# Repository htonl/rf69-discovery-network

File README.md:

This is the network library for the ALog by Northern Widget. This was developed
by Luke Cesarz, Jeff Worm, and David Nickel

This repo contains 2 branches:
master                      //Implemented with low power lab lib
feather-version             //Implemented with feather

The feather-version branch is the version of the code that was working on the
M0. We had a zero acting as coord with two pros sending it data flawlessly.
I think we then made a change to test something and broke it.

Both libraries work with the arduino pro.

The reason we have both libraries is SPI. SPI setup in the low power lab library
is not working on the M0, but the SPI setup in feather does work with the M0.

The issue in the feather-version can be described like so:
When we get to transmission, the radio reaches a stand still and the code
deadlocks. It is marked in the file where we suspect this is happening. It is in
the RH_RF69.cpp file.

It happens when we call sendToWait()

The files we added:
Network.h           //Self discovery algorithm and communication protocol
Network.cpp         // ''
Queue.cpp           //The queue for storing the data to send
Queue.h             //''
Packet.h            //The packet stucture we designed for communication

DESCRIPTION OF HOW THE NETWORK: I WROTE THIS A WHILE AGO, BUT IT IS STILL A GOOD
DESCRIPTION -LUKE

This code is meant to interface with the Alog library by Northern Widget. When
completed, this implementation will include radio telemetry using the RFM69 chip
for RF communication. This library is currently a work in progress and should
not be expected to work on its own. Expect a working copy in early May.
The new libraries in this repo are the Network.cpp, Network.h, Queue.cpp,
Queue.h, and Packet.h files. In total about 650 lines of code were added.

How to use the Network:

In order to use the network in the Logger Library, the user need only call 2
functions: sendOverNetwork(float data) with a floating point of the data that
they want to send to the coord, and then runNetwork(). runNetwork() is the
heart of the network library. It takes care of keeping up each nodes connection
to the coordinator, and handling any packets it receives or needs to send. A 
more detailed description of the algorithm can be found below, but these two
functions are all the end user NEEDS to get the network rolling.

A more detailed description:

The network algorithm works like so in pseudocode:

runNetwork()
{
	//condition 1 we are the coord listen for data
	if(IamCoord)
	{
		listen for incoming data and upload it to server
	}
	//condition 2 we have a connection to the coord, send data
	else if(IhaveConnectionToCoord)
	{
		send all of my data towards coord
		listen for data to forward to coord
	}
	//condition 3 we do not have connection to the coord
	else
	{
		try to connect to coordinator
	}
}
A few notable points in this algorithm. Originally, we were trying to forward
the data from the furthest leaf nodes to the router nodes first, then forward it
to the coordinator, but there is a nightmare of timing issues and other
complexities. Then we decided to do the opposite:send the data from the closest
nodes to the coordinator first. Therefore in condition 2, all the nodes that
aren't coord will be sending their data over and over again until it finally
reaches the coordinator. Then they will start listening for other nodes that
are using them as a next hop to get to the coord, and forward that data. This
eliminates a lot of the timing issues, and the need for each node to know the
other nodes depending on it.

Data logger library for the Arduino-based ALog (http://northernwidget.com/?page_id=8)

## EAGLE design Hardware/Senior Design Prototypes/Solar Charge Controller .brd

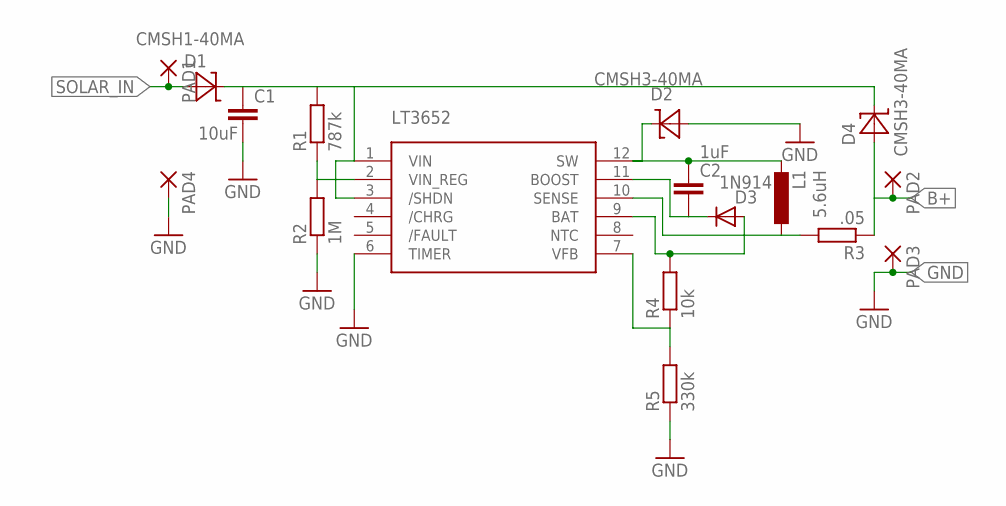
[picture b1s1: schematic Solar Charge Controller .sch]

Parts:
C1: 10uF; C0805
C2: 1uF; C0603
D1: CMSH1-40MA; DO-214AC
D2, D4: CMSH3-40MA; DO-214AC
D3: 1N914; SOD523
L1: 5.6uH; 1008(2510METRIC)
PAD1, PAD2, PAD3, PAD4: SMD5; SMD2,54-5,08
R1: 787k; R0603
R2: 1M; R0603
R3: .05; R0805
R4: 10k; R0603
R5: 330k; R0603
U$1: LT3652; MSOP12

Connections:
B+: D4.A, PAD2.1, R3.1
GND: C1.2, D2.A, PAD3.1, PAD4.1, R2.1, R5.1, U$1.6 (TIMER)
unnamed: C1.1, D1.C, D4.C, R1.2, U$1.1 (VIN), U$1.3 (/SHDN)
unnamed: R1.1, R2.2, U$1.2 (VIN_REG)
unnamed: C2.1, D2.C, L1.P$3 (2), U$1.12 (SW)
unnamed: L1.P$2 (1), R3.2, U$1.10 (SENSE)
unnamed: D3.A, R4.2, U$1.9 (BAT)
unnamed: C2.2, D3.C, U$1.11 (BOOST)
unnamed: R4.1, R5.2, U$1.7 (VFB)
SOLAR_IN: D1.A, PAD1.1

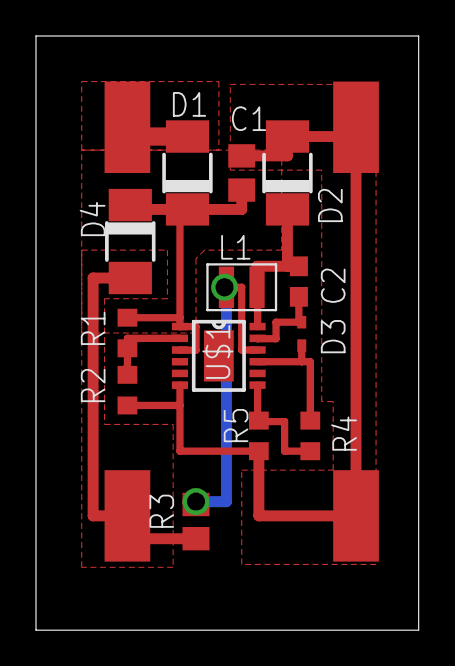
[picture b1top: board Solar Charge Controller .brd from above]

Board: 2 copper layers, 21.3 x 33.0 mm, 17 parts (0 on the bottom side), 10 nets.

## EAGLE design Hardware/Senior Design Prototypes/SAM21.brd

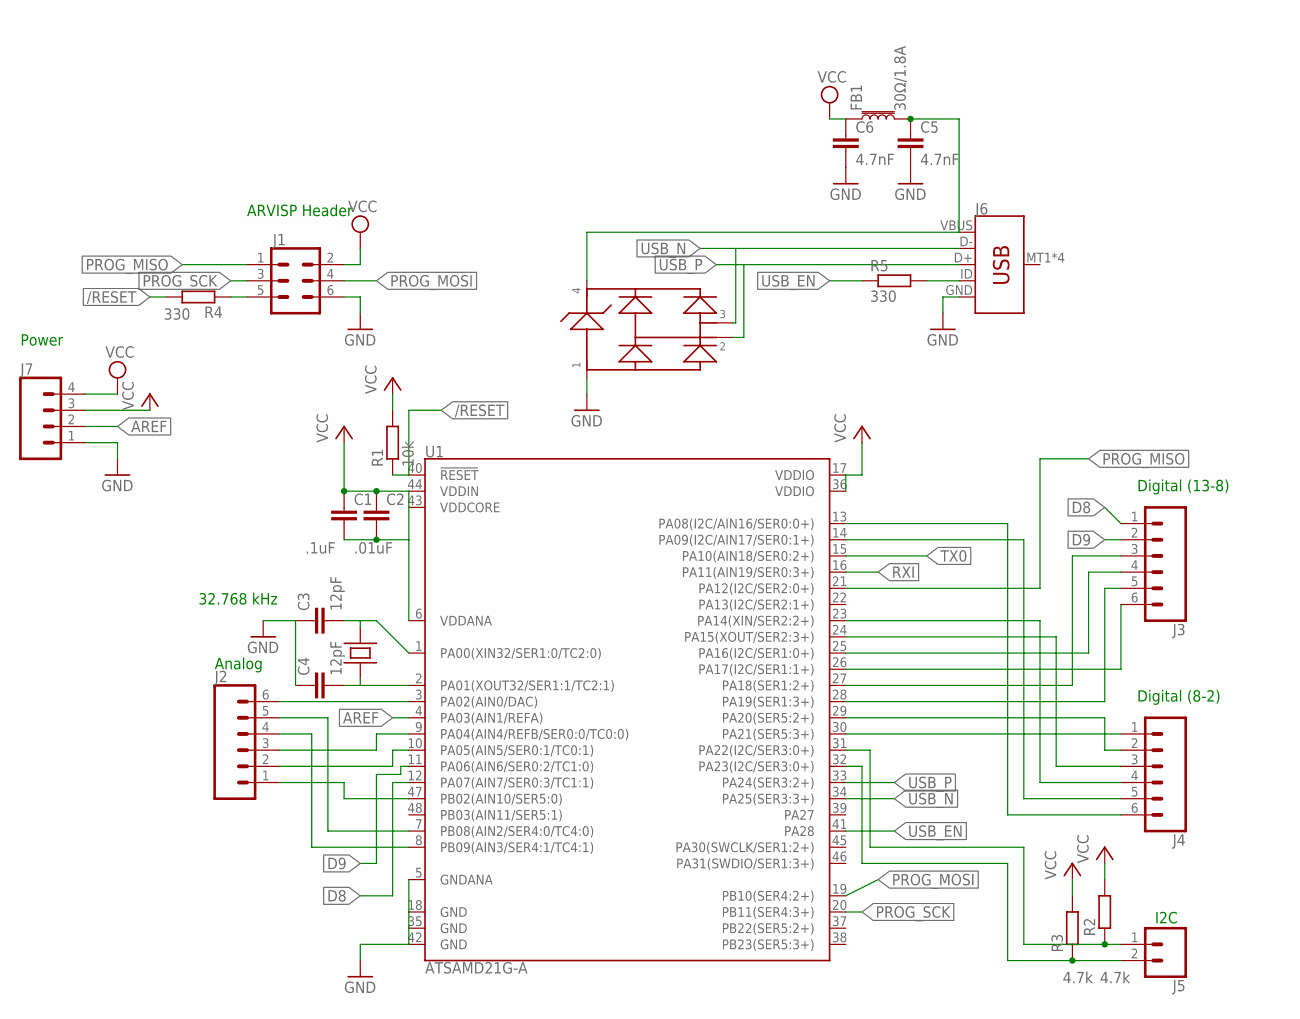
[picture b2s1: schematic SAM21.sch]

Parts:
C1: .1uF; C0603
C2: .01uF; C0603
C3, C4: 12pF; C0603
C5, C6: 4.7nF; C0603
FB1: 30Ω/1.8A; 0603
J1: CONN_03X2FEMALE_SMD; 2X3_SMD
J2, J3, J4: CONN_06LONGPADS; 1X06_LONGPADS
J5: CONN_02PTH3; 1X02_LONGPADS
J6: USB_MICRO-B_SMT; USB-MICROB
J7: CONN_04LONGPADS; 1X04_LONGPADS
R1: 10k; R0603
R2, R3: 4.7k; R0603
R4, R5: 330; R0603
U1: ATSAMD21G-A; TQFP-48
U$1: CM200; 4-SOJ
U$2: PRTR5V0U2X; SOT143B

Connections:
5V: J1.2
/RESET: R1.1, R4.2, U1.40 (!RESET!)
AREF: J7.2, U1.4 (PA03(AIN1/REFA))
D8: J3.1, U1.12 (PA07(AIN7/SER0:3/TC1:1))
D9: J2.4, J3.2, U1.8 (PB09(AIN3/SER4:1/TC4:1)), U1.11 (PA06(AIN6/SER0:2/TC1:0))
GND: C3.1, C4.1, C5.2, C6.2, J1.6, J6.GND, J7.1, U1.5 (GNDANA), U1.18 (GND), U1.35 (GND), U1.42 (GND), U$2.P$1 (1)
unnamed: J4.1, U1.30 (PA21(SER5:3+))
unnamed: J2.6, U1.3 (PA02(AIN0/DAC))
unnamed: J2.5, U1.7 (PB08(AIN2/SER4:0/TC4:0))
unnamed: J4.2, U1.29 (PA20(SER5:2+))
unnamed: J2.3, U1.9 (PA04(AIN4/REFB/SER0:0/TC0:0))
unnamed: J2.2, U1.10 (PA05(AIN5/SER0:1/TC0:1))
unnamed: J2.1, U1.47 (PB02(AIN10/SER5:0))
unnamed: J3.6, U1.26 (PA17(I2C/SER1:1+))
unnamed: J3.5, U1.28 (PA19(SER1:3+))
unnamed: J3.4, U1.25 (PA16(I2C/SER1:0+))
unnamed: J3.3, U1.27 (PA18(SER1:2+))
unnamed: J4.3, U1.24 (PA15(XOUT/SER2:3+))
unnamed: J4.4, U1.23 (PA14(XIN/SER2:2+))
unnamed: J4.5, U1.14 (PA09(I2C/AIN17/SER0:1+))
unnamed: J4.6, U1.13 (PA08(I2C/AIN16/SER0:0+))
unnamed: U1.17 (VDDIO), U1.36 (VDDIO)
unnamed: J5.1, R2.1, U1.31 (PA22(I2C/SER3:0+))
unnamed: C4.2, U1.2 (PA01(XOUT32/SER1:1/TC2:1)), U$1.P$1
unnamed: J5.2, R3.1, U1.32 (PA23(I2C/SER3:0+))
unnamed: J1.5, R4.1
unnamed: C3.2, U1.1 (PA00(XIN32/SER1:0/TC2:0)), U$1.P$4
unnamed: C5.1, FB1.2, J6.VBUS, U$2.P$4 (4)
unnamed: J6.ID, R5.2
PROG_MISO: J1.1, U1.21 (PA12(I2C/SER2:0+))
PROG_MOSI: J1.4, U1.19 (PB10(SER4:2+))
PROG_SCK: J1.3, U1.20 (PB11(SER4:3+))
RXI: U1.16 (PA11(AIN19/SER0:3+))
TX0: U1.15 (PA10(AIN18/SER0:2+))
USB_EN: R5.1, U1.41 (PA28)
USB_N: J6.D-, U1.34 (PA25(SER3:3+)), U$2.P$3 (3)
USB_P: J6.D+, U1.33 (PA24(SER3:2+)), U$2.P$2 (2)
VCC: C1.1, C1.2, C2.1, C2.2, C6.1, FB1.1, J7.3, J7.4, R1.2, R2.2, R3.2, U1.6 (VDDANA), U1.43 (VDDCORE), U1.44 (VDDIN)

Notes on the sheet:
ARVISP Header
Analog
Digital (13-8)
Digital (8-2)
I2C
32.768 kHz
Power

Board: 2 copper layers, 22 parts (0 on the bottom side), 35 nets, no tracks yet.

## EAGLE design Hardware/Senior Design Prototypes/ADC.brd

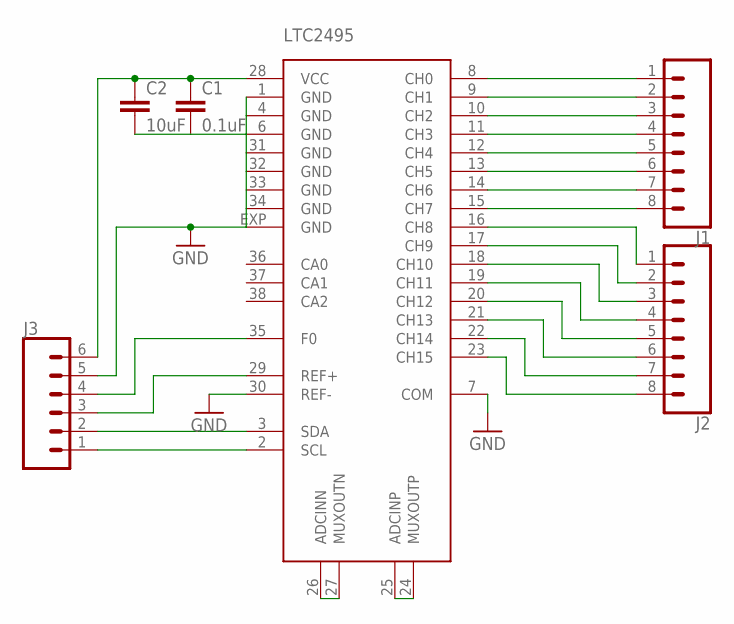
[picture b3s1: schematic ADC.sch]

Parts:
C1: 0.1uF; C0603
C2: 10uF; C0805
J1, J2: CONN_08LONGPADS; 1X08_LONGPADS
J3: CONN_06LONGPADS; 1X06_LONGPADS
U$1: LTC2495; QFN38-5X7

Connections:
GND: C1.2, C2.2, J3.5, U$1.1 (GND), U$1.4 (GND), U$1.6 (GND), U$1.7 (COM), U$1.30 (REF-), U$1.31 (GND), U$1.32 (GND), U$1.33 (GND), U$1.34 (GND), U$1.EXP (GND)
unnamed: J3.1, U$1.2 (SCL)
unnamed: J3.2, U$1.3 (SDA)
unnamed: J3.3, U$1.29 (REF+)
unnamed: J3.4, U$1.35 (F0)
unnamed: C1.1, C2.1, J3.6, U$1.28 (VCC)
unnamed: U$1.26 (ADCINN), U$1.27 (MUXOUTN)
unnamed: U$1.24 (MUXOUTP), U$1.25 (ADCINP)
unnamed: J1.8, U$1.15 (CH7)
unnamed: J1.7, U$1.14 (CH6)
unnamed: J1.6, U$1.13 (CH5)
unnamed: J1.5, U$1.12 (CH4)
unnamed: J1.4, U$1.11 (CH3)
unnamed: J1.3, U$1.10 (CH2)
unnamed: J1.2, U$1.9 (CH1)
unnamed: J1.1, U$1.8 (CH0)
unnamed: J2.1, U$1.16 (CH8)
unnamed: J2.2, U$1.17 (CH9)
unnamed: J2.3, U$1.18 (CH10)
unnamed: J2.4, U$1.19 (CH11)
unnamed: J2.5, U$1.20 (CH12)
unnamed: J2.6, U$1.21 (CH13)
unnamed: J2.7, U$1.22 (CH14)
unnamed: J2.8, U$1.23 (CH15)

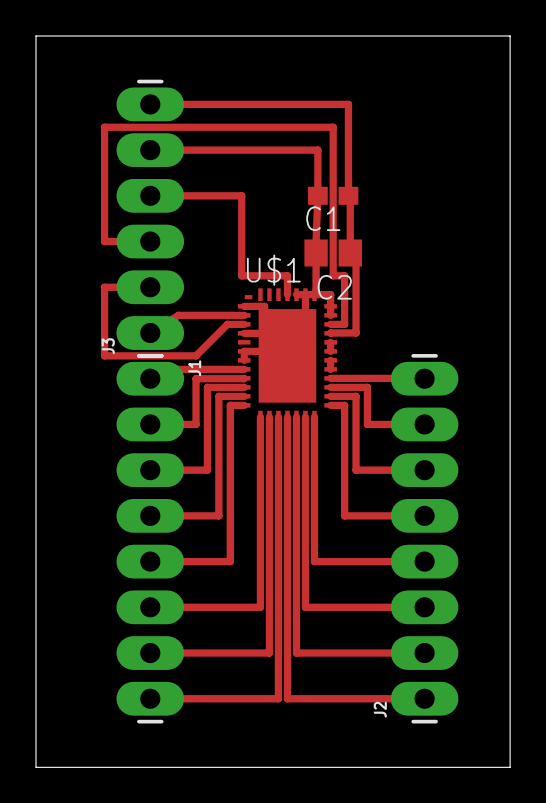
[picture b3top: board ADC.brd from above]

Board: 2 copper layers, 26.3 x 40.6 mm, 6 parts (0 on the bottom side), 24 nets.

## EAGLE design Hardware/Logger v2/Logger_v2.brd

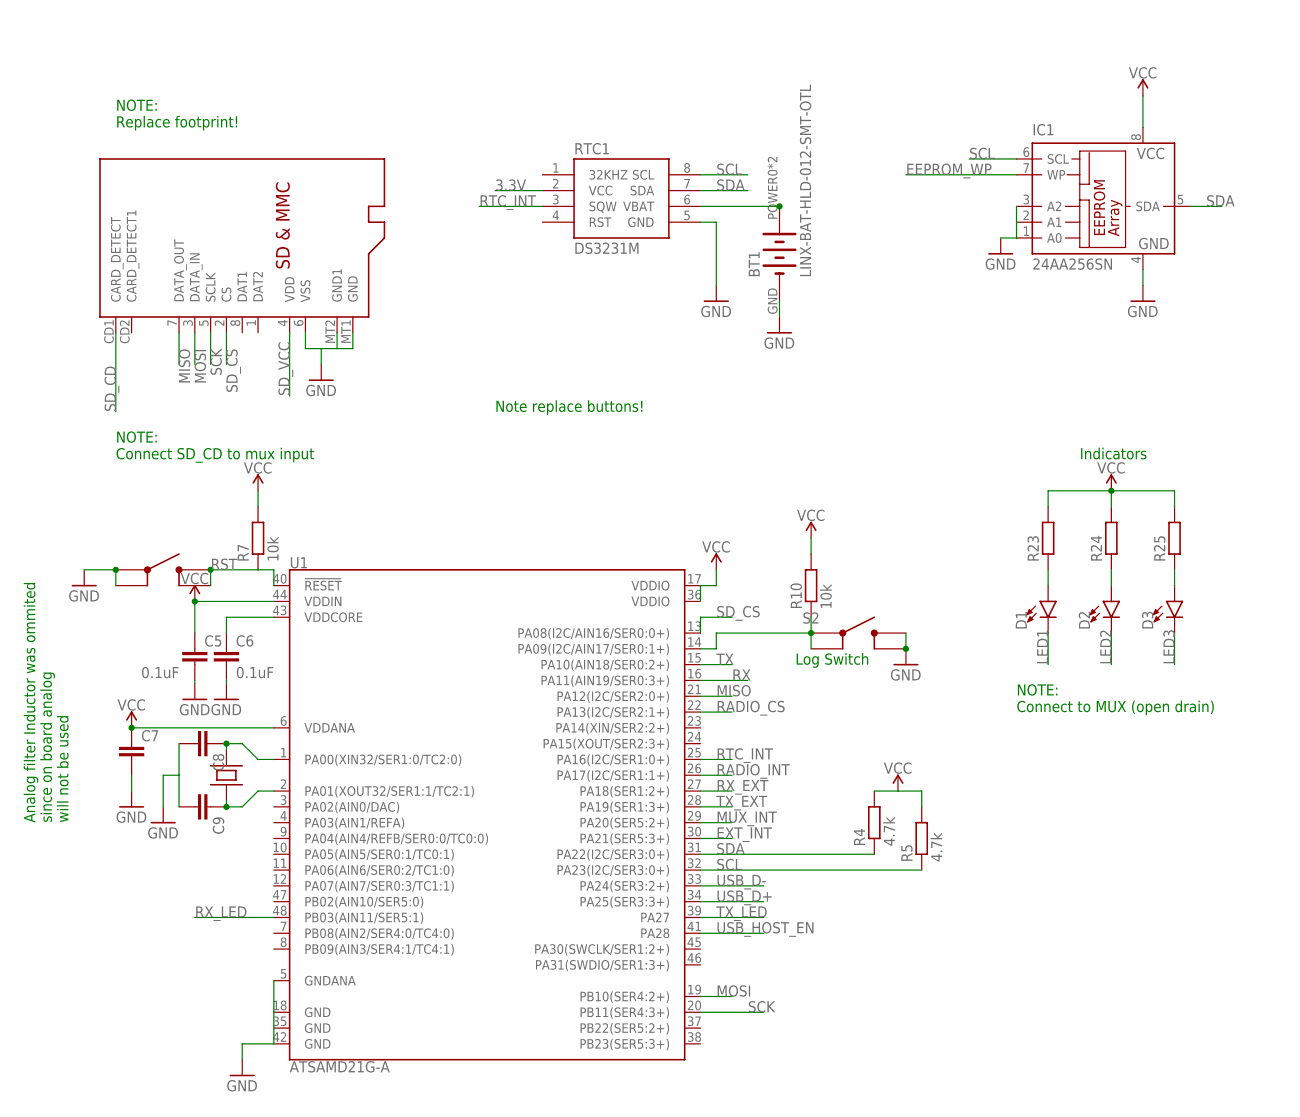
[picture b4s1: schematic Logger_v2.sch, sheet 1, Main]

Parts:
BT1: LINX-BAT-HLD-012-SMT-OTL; LINX_BAT-HLD-012-SMT
C5, C6: 0.1uF; C0603
C7, C8, C9: C-EUC0603; C0603
D1, D2, D3: LED0603; LED-0603
IC1: 24AA256SN; SO-08
R4, R5: 4.7k; R0603
R7, R10: 10k; R0603
R23, R24, R25: R-EU_R0603; R0603
RTC1: DS3231M; SO08
S2: SKRPABE010; SKRPABE010_(SWITCH)
U1: ATSAMD21G-A; TQFP-48
U$1: SKRPABE010; SKRPABE010_(SWITCH)
U$2: MICROSD
U$5: CM200; 4-SOJ

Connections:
3.3V: C5.1, C7.1, IC1.8 (VCC), R4.2, R5.2, R7.2, R10.2, R23.2, R24.2, R25.2, RTC1.2 (VCC), U1.6 (VDDANA), U1.17 (VDDIO), U1.36 (VDDIO), U1.44 (VDDIN); also elsewhere on the board
EEPROM_WP: IC1.7 (WP)
EXT_INT: U1.30 (PA21(SER5:3+)); also elsewhere on the board
GND: BT1.GND (-), C5.2, C6.2, C7.2, C8.2, C9.2, IC1.1 (A0), IC1.2 (A1), IC1.3 (A2), IC1.4 (GND), RTC1.5 (GND), S2.P$3 (3), S2.P$4 (4), U1.5 (GNDANA), U1.18 (GND), U1.42 (GND), U$1.P$1 (1), U$1.P$2 (2), U$2.6 (VSS), U$2.MT1 (GND), U$2.MT2 (GND1); also elsewhere on the board
LED1: D1.C; also elsewhere on the board
LED2: D2.C; also elsewhere on the board
LED3: D3.C; also elsewhere on the board
MISO: U1.21 (PA12(I2C/SER2:0+)), U$2.7 (DATA_OUT); also elsewhere on the board
MOSI: U1.19 (PB10(SER4:2+)), U$2.3 (DATA_IN); also elsewhere on the board
MUX_INT: U1.29 (PA20(SER5:2+)); also elsewhere on the board
unnamed: R10.1, S2.P$1 (1), S2.P$2 (2), U1.14 (PA09(I2C/AIN17/SER0:1+))
unnamed: C6.1, U1.43 (VDDCORE)
unnamed: C8.1, U1.1 (PA00(XIN32/SER1:0/TC2:0)), U$5.P$4
unnamed: C9.1, U1.2 (PA01(XOUT32/SER1:1/TC2:1)), U$5.P$1
unnamed: BT1.POWER0 (+), BT1.POWER1 (+), RTC1.6 (VBAT)
unnamed: D1.A, R23.1
unnamed: D2.A, R24.1
unnamed: D3.A, R25.1
RADIO_CS: U1.22 (PA13(I2C/SER2:1+)); also elsewhere on the board
RADIO_INT: U1.26 (PA17(I2C/SER1:1+)); also elsewhere on the board
RST: R7.1, U1.40 (!RESET!), U$1.P$3 (3), U$1.P$4 (4); also elsewhere on the board
RTC_INT: RTC1.3 (SQW), U1.25 (PA16(I2C/SER1:0+))
RX: U1.16 (PA11(AIN19/SER0:3+))
RX_EXT: U1.27 (PA18(SER1:2+)); also elsewhere on the board
RX_LED: U1.48 (PB03(AIN11/SER5:1))
SCK: U1.20 (PB11(SER4:3+)), U$2.5 (SCLK); also elsewhere on the board
SCL: IC1.6 (SCL), R5.1, RTC1.8 (SCL), U1.32 (PA23(I2C/SER3:0+)); also elsewhere on the board
SDA: IC1.5 (SDA), R4.1, RTC1.7 (SDA), U1.31 (PA22(I2C/SER3:0+)); also elsewhere on the board
SD_CD: U$2.CD1 (CARD_DETECT)
SD_CS: U1.13 (PA08(I2C/AIN16/SER0:0+)), U$2.2 (CS)
SD_VCC: U$2.4 (VDD); also elsewhere on the board
TX: U1.15 (PA10(AIN18/SER0:2+))
TX_EXT: U1.28 (PA19(SER1:3+)); also elsewhere on the board
TX_LED: U1.39 (PA27)
USB_D+: U1.34 (PA25(SER3:3+)); also elsewhere on the board
USB_D-: U1.33 (PA24(SER3:2+)); also elsewhere on the board
USB_HOST_EN: U1.41 (PA28); also elsewhere on the board

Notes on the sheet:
NOTE: Replace footprint!
Log Switch
Analog filter Inductor was ommited since on board analog will not be used
Indicators
NOTE: Connect to MUX (open drain)
NOTE: Connect SD_CD to mux input
Note replace buttons!

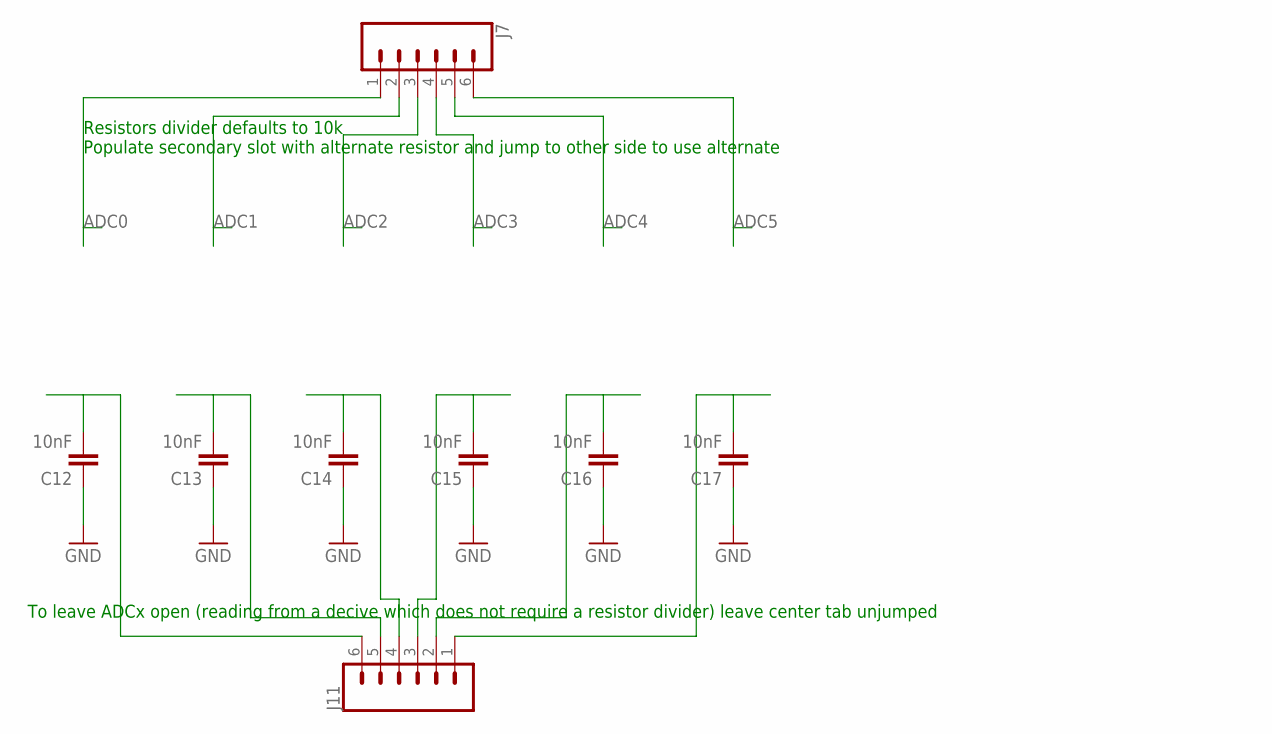
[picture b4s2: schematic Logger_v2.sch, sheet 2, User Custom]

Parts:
C12, C13, C14, C15, C16, C17: 10nF; C0603
J7, J11: CONN_06SMD-STRAIGHT-FEMALE; 1X06_SMD_STRAIGHT

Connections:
ADC0: J7.1; also elsewhere on the board
ADC1: J7.2; also elsewhere on the board
ADC2: J7.3; also elsewhere on the board
ADC3: J7.4; also elsewhere on the board
ADC4: J7.5; also elsewhere on the board
ADC5: J7.6; also elsewhere on the board
GND: C12.1, C13.1, C14.1, C15.1, C16.1, C17.1; also elsewhere on the board
unnamed: C12.2, J11.6
unnamed: C13.2, J11.5
unnamed: C14.2, J11.4
unnamed: C15.2, J11.3
unnamed: C16.2, J11.2
unnamed: C17.2, J11.1

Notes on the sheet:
Resistors divider defaults to 10k Populate secondary slot with alternate resistor and jump to other side to use alternate
To leave ADCx open (reading from a decive which does not require a resistor divider) leave center tab unjumped

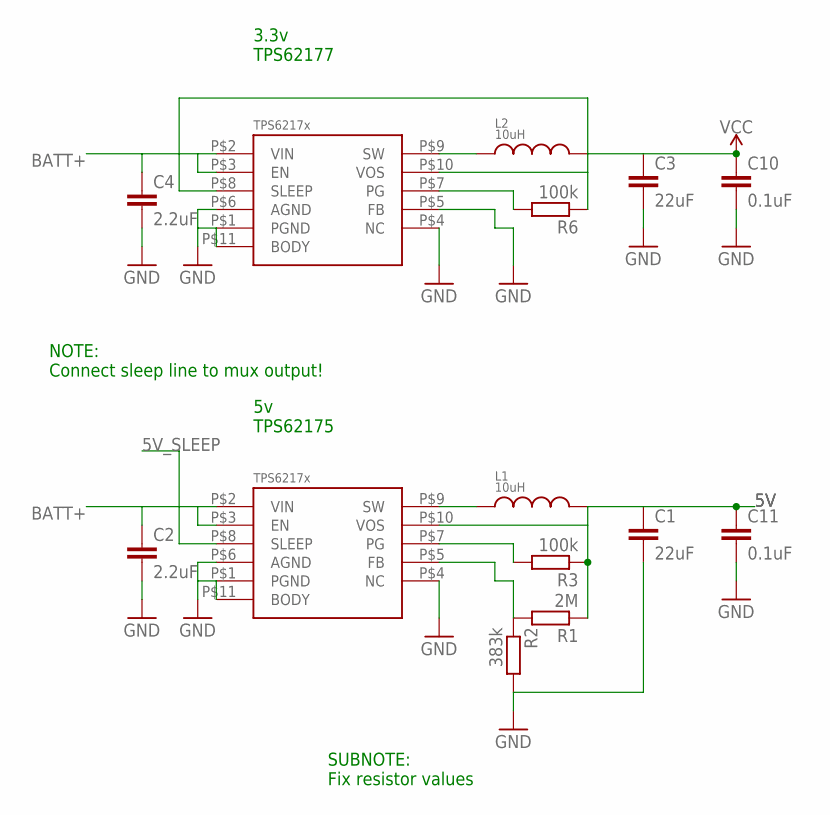
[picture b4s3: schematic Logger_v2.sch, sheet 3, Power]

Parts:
C1, C3: 22uF; C1210
C2, C4: 2.2uF; C0603
C10, C11: 0.1uF; C0603
L1, L2: 10uH; WE-LQS(INDUCTOR)
R1: 2M; R0603
R2: 383k; R0603
R3, R6: 100k; R0603
U$3, U$4: TPS6217X; WSON-10

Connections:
3.3V: C3.1, C10.1, L2.P$2, R6.1, U$4.P$8 (SLEEP), U$4.P$10 (VOS); also elsewhere on the board
5V: C1.1, C11.1, L1.P$2, R1.1, R3.1, U$3.P$10 (VOS); also elsewhere on the board
5V_SLEEP: U$3.P$8 (SLEEP)
BATT+: C2.1, C4.1, U$3.P$2 (VIN), U$3.P$3 (EN), U$4.P$2 (VIN), U$4.P$3 (EN); also elsewhere on the board
GND: C1.2, C2.2, C3.2, C4.2, C10.2, C11.2, R2.2, U$3.P$1 (PGND), U$3.P$4 (NC), U$3.P$6 (AGND), U$3.P$11 (BODY), U$4.P$1 (PGND), U$4.P$4 (NC), U$4.P$5 (FB), U$4.P$6 (AGND), U$4.P$11 (BODY); also elsewhere on the board
unnamed: L1.P$1, U$3.P$9 (SW)
unnamed: L2.P$1, U$4.P$9 (SW)
unnamed: R1.2, R2.1, U$3.P$5 (FB)
unnamed: R3.2, U$3.P$7 (PG)
unnamed: R6.2, U$4.P$7 (PG)

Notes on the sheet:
3.3v TPS62177
5v TPS62175
NOTE: Connect sleep line to mux output!
SUBNOTE: Fix resistor values

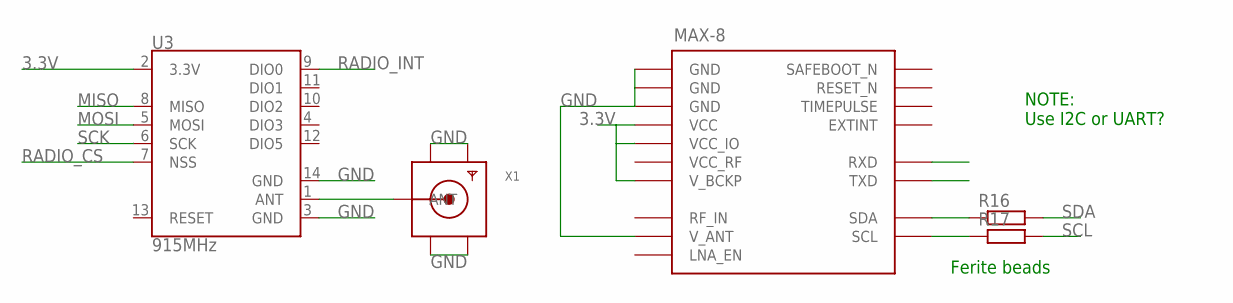
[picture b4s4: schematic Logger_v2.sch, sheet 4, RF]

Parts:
R16, R17: R-EU_R0603; R0603
U3: 915MHz; RFM69CW-XXXS2
U$6: UBLOX_MAX-8; MAX-8
X1: SMACONNECTOR_EDGE; SMA_EDGELAUNCH

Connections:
3.3V: U3.2 (3.3V), U$6.P$6 (V_BCKP), U$6.P$7 (VCC_IO), U$6.P$8 (VCC); also elsewhere on the board
GND: U3.3 (GND), U3.14 (GND), U$6.P$1 (GND), U$6.P$10 (GND), U$6.P$12 (GND), U$6.P$15 (V_ANT), X1.GND@1 (GND4), X1.GND@2 (GND3), X1.GND@3 (GND2), X1.GND@4 (GND1); also elsewhere on the board
MISO: U3.8 (MISO); also elsewhere on the board
MOSI: U3.5 (MOSI); also elsewhere on the board
unnamed: R16.1, U$6.P$16 (SDA)
unnamed: R17.1, U$6.P$17 (SCL)
unnamed: U3.1 (ANT), X1.P (ANT)
RADIO_CS: U3.7 (NSS); also elsewhere on the board
RADIO_INT: U3.9 (DIO0); also elsewhere on the board
SCK: U3.6 (SCK); also elsewhere on the board
SCL: R17.2; also elsewhere on the board
SDA: R16.2; also elsewhere on the board
VCC_RF: U$6.P$14 (VCC_RF)

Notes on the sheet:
NOTE: Use I2C or UART?
Ferite beads

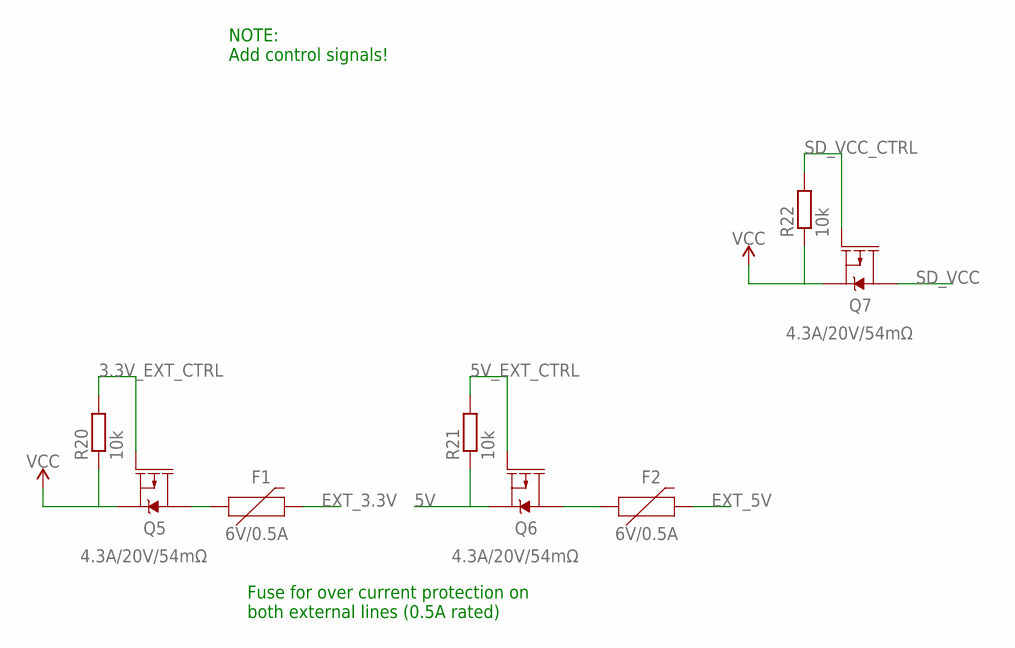
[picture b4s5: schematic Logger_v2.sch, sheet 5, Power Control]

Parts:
F1, F2: 6V/0.5A; 1206
Q5, Q6, Q7: 4.3A/20V/54mΩ; SOT23-3
R20, R21, R22: 10k; R0603

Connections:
3.3V: Q5.2 (S), Q7.2 (S), R20.1, R22.1; also elsewhere on the board
3.3V_EXT_CTRL: Q5.1 (G), R20.2; also elsewhere on the board
5V: Q6.2 (S), R21.1; also elsewhere on the board
5V_EXT_CTRL: Q6.1 (G), R21.2; also elsewhere on the board
EXT_3.3V: F1.2; also elsewhere on the board
EXT_5V: F2.2; also elsewhere on the board
unnamed: F1.1, Q5.3 (D)
unnamed: F2.1, Q6.3 (D)
SD_VCC: Q7.3 (D); also elsewhere on the board
SD_VCC_CTRL: Q7.1 (G), R22.2; also elsewhere on the board

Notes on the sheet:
NOTE: Add control signals!
Fuse for over current protection on both external lines (0.5A rated)

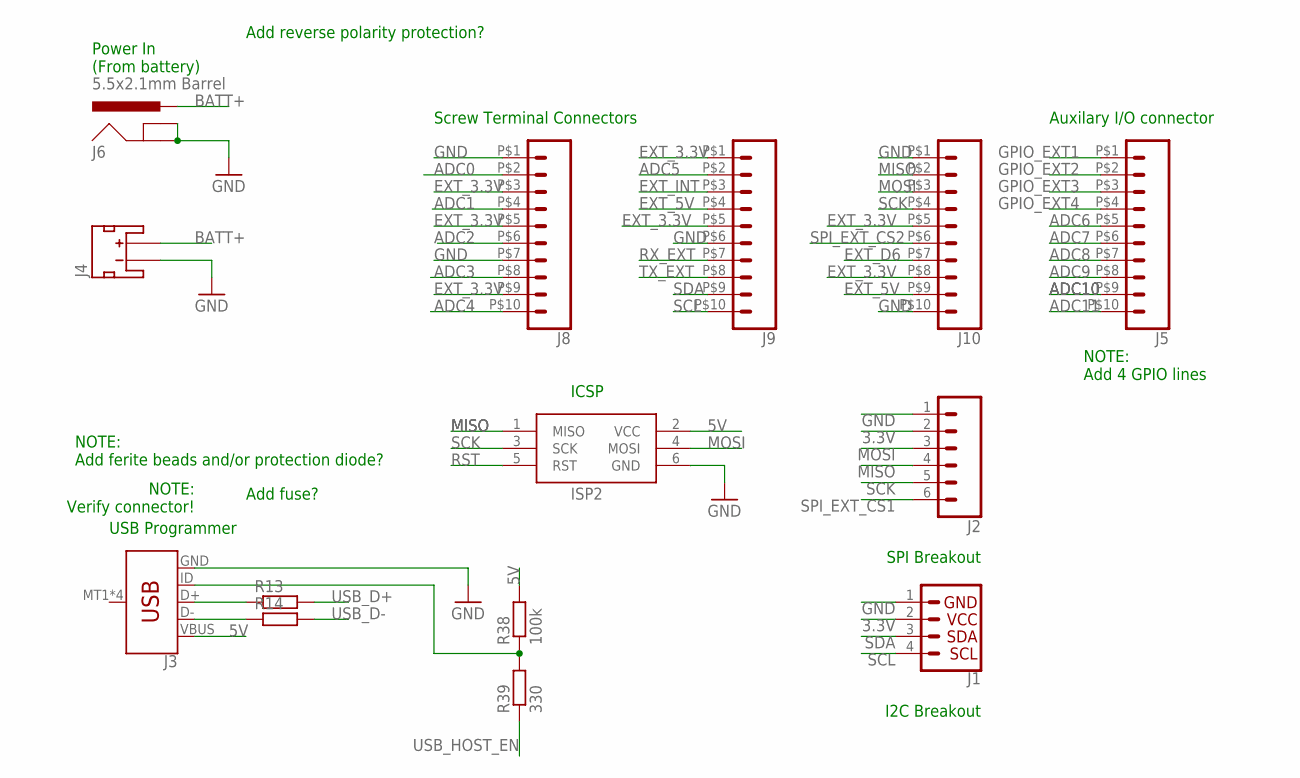
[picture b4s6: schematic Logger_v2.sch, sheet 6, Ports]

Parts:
ISP2: AVRISP-6; AVRISP
J1: I2C_STANDARD; 1X04
J2: CONN_06SILK_FEMALE_PTH; 1X06
J3: USB_MICRO-B_SMT; USB-MICROB
J4: JST_2MM_MALE; JST-2-SMD
J5, J8, J9, J10: CONN_10; SCREWTERMINAL-3.5MM-10
J6: 5.5x2.1mm Barrel; POWER_JACK_SMD
R13, R14: R-EU_R0603; R0603
R38: 100k; R0603
R39: 330; R0603

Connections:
3.3V: J1.2, J2.2; also elsewhere on the board
5V: ISP2.2 (VCC), J3.VBUS, R38.2; also elsewhere on the board
ADC0: J8.P$2 (2); also elsewhere on the board
ADC1: J8.P$4 (4); also elsewhere on the board
ADC2: J8.P$6 (6); also elsewhere on the board
ADC3: J8.P$8 (8); also elsewhere on the board
ADC4: J8.P$10 (10); also elsewhere on the board
ADC5: J9.P$2 (2); also elsewhere on the board
ADC6: J5.P$5 (5); also elsewhere on the board
ADC7: J5.P$6 (6); also elsewhere on the board
ADC8: J5.P$7 (7); also elsewhere on the board
ADC9: J5.P$8 (8); also elsewhere on the board
ADC10: J5.P$9 (9); also elsewhere on the board
ADC11: J5.P$10 (10); also elsewhere on the board
BATT+: J4.2 (+), J6.VIN0 (PWR); also elsewhere on the board
EXT_3.3V: J8.P$3 (3), J8.P$5 (5), J8.P$9 (9), J9.P$1 (1), J9.P$5 (5), J10.P$5 (5), J10.P$8 (8); also elsewhere on the board
EXT_5V: J9.P$4 (4), J10.P$9 (9); also elsewhere on the board
EXT_D6: J10.P$7 (7); also elsewhere on the board
EXT_INT: J9.P$3 (3); also elsewhere on the board
GND: ISP2.6 (GND), J1.1, J2.1, J3.GND, J4.1 (-), J6.GND (GNDBREAK), J6.P$4 (GND), J8.P$1 (1), J8.P$7 (7), J9.P$6 (6), J10.P$1 (1), J10.P$10 (10); also elsewhere on the board
GPIO_EXT1: J5.P$1 (1); also elsewhere on the board
GPIO_EXT2: J5.P$2 (2); also elsewhere on the board
GPIO_EXT3: J5.P$3 (3); also elsewhere on the board
GPIO_EXT4: J5.P$4 (4); also elsewhere on the board
MISO: ISP2.1 (MISO), J2.4, J10.P$2 (2); also elsewhere on the board
MOSI: ISP2.4 (MOSI), J2.3, J10.P$3 (3); also elsewhere on the board
unnamed: J3.D+, R13.1
unnamed: J3.D-, R14.1
unnamed: J3.ID, R38.1, R39.2
RST: ISP2.5 (RST); also elsewhere on the board
RX_EXT: J9.P$7 (7); also elsewhere on the board
SCK: ISP2.3 (SCK), J2.5, J10.P$4 (4); also elsewhere on the board
SCL: J1.4, J9.P$10 (10); also elsewhere on the board
SDA: J1.3, J9.P$9 (9); also elsewhere on the board
SPI_EXT_CS1: J2.6; also elsewhere on the board
SPI_EXT_CS2: J10.P$6 (6); also elsewhere on the board
TX_EXT: J9.P$8 (8); also elsewhere on the board
USB_D+: R13.2; also elsewhere on the board
USB_D-: R14.2; also elsewhere on the board
USB_HOST_EN: R39.1; also elsewhere on the board

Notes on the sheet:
Power In (From battery)
Add reverse polarity protection?
I2C Breakout
SPI Breakout
NOTE: Verify connector!
Add fuse?
NOTE: Add ferite beads and/or protection diode?
Screw Terminal Connectors
ICSP
USB Programmer
Auxilary I/O connector
NOTE: Add 4 GPIO lines

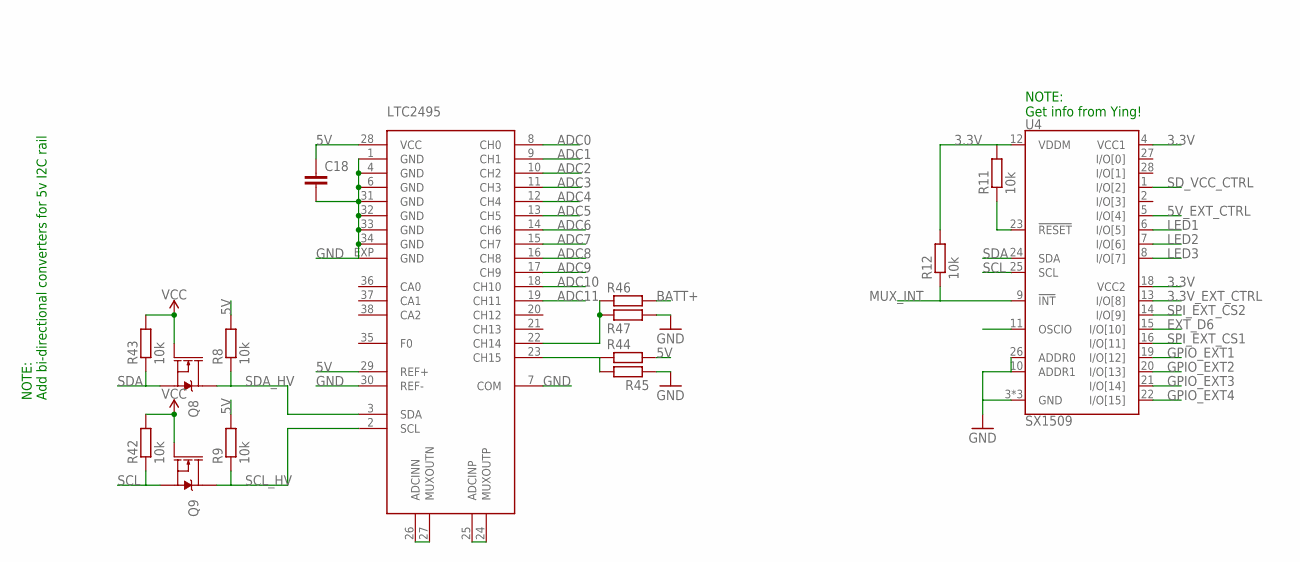
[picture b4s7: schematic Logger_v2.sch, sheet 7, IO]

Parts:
C18: C-EUC0603; C0603
Q8, Q9: 220mA/50V/3.5Ω; SOT23-3
R8, R9, R11, R12, R42, R43: 10k; R0603
R44, R45, R46, R47: R-EU_R0603; R0603
U4: SX1509; QFN-28
U$7: LTC2495; QFN38-5X7

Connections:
3.3V: Q8.1 (G), Q9.1 (G), R11.2, R12.2, R42.2, R43.2, U4.4 (VCC1), U4.12 (VDDM), U4.18 (VCC2); also elsewhere on the board
3.3V_EXT_CTRL: U4.13 (I/O[8]); also elsewhere on the board
5V: C18.1, R8.2, R9.2, R44.2, U$7.28 (VCC), U$7.29 (REF+); also elsewhere on the board
5V_EXT_CTRL: U4.5 (I/O[4]); also elsewhere on the board
ADC0: U$7.8 (CH0); also elsewhere on the board
ADC1: U$7.9 (CH1); also elsewhere on the board
ADC2: U$7.10 (CH2); also elsewhere on the board
ADC3: U$7.11 (CH3); also elsewhere on the board
ADC4: U$7.12 (CH4); also elsewhere on the board
ADC5: U$7.13 (CH5); also elsewhere on the board
ADC6: U$7.14 (CH6); also elsewhere on the board
ADC7: U$7.15 (CH7); also elsewhere on the board
ADC8: U$7.16 (CH8); also elsewhere on the board
ADC9: U$7.17 (CH9); also elsewhere on the board
ADC10: U$7.18 (CH10); also elsewhere on the board
ADC11: U$7.19 (CH11); also elsewhere on the board
BATT+: R46.2; also elsewhere on the board
EXT_D6: U4.15 (I/O[10]); also elsewhere on the board
GND: C18.2, R45.1, R47.2, U4.3 (GND), U4.10 (ADDR1), U4.17 (GND), U4.26 (ADDR0), U4.29 (GND), U$7.1 (GND), U$7.4 (GND), U$7.6 (GND), U$7.7 (COM), U$7.30 (REF-), U$7.31 (GND), U$7.32 (GND), U$7.33 (GND), U$7.34 (GND), U$7.EXP (GND); also elsewhere on the board
GPIO_EXT1: U4.19 (I/O[12]); also elsewhere on the board
GPIO_EXT2: U4.20 (I/O[13]); also elsewhere on the board
GPIO_EXT3: U4.21 (I/O[14]); also elsewhere on the board
GPIO_EXT4: U4.22 (I/O[15]); also elsewhere on the board
LED1: U4.6 (I/O[5]); also elsewhere on the board
LED2: U4.7 (I/O[6]); also elsewhere on the board
LED3: U4.8 (I/O[7]); also elsewhere on the board
MUX_INT: R12.1, U4.9 (!INT); also elsewhere on the board
unnamed: U$7.26 (ADCINN), U$7.27 (MUXOUTN)
unnamed: U$7.24 (MUXOUTP), U$7.25 (ADCINP)
unnamed: R44.1, R45.2, U$7.23 (CH15)
unnamed: R46.1, R47.1, U$7.22 (CH14)
unnamed: R11.1, U4.23 (!RESET)
SCL: Q9.2 (S), R42.1, U4.25 (SCL); also elsewhere on the board
SCL_HV: Q9.3 (D), R9.1, U$7.2 (SCL)
SDA: Q8.2 (S), R43.1, U4.24 (SDA); also elsewhere on the board
SDA_HV: Q8.3 (D), R8.1, U$7.3 (SDA)
SD_VCC_CTRL: U4.1 (I/O[2]); also elsewhere on the board
SPI_EXT_CS1: U4.16 (I/O[11]); also elsewhere on the board
SPI_EXT_CS2: U4.14 (I/O[9]); also elsewhere on the board

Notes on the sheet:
NOTE: Add bi-directional converters for 5v I2C rail
NOTE: Get info from Ying!

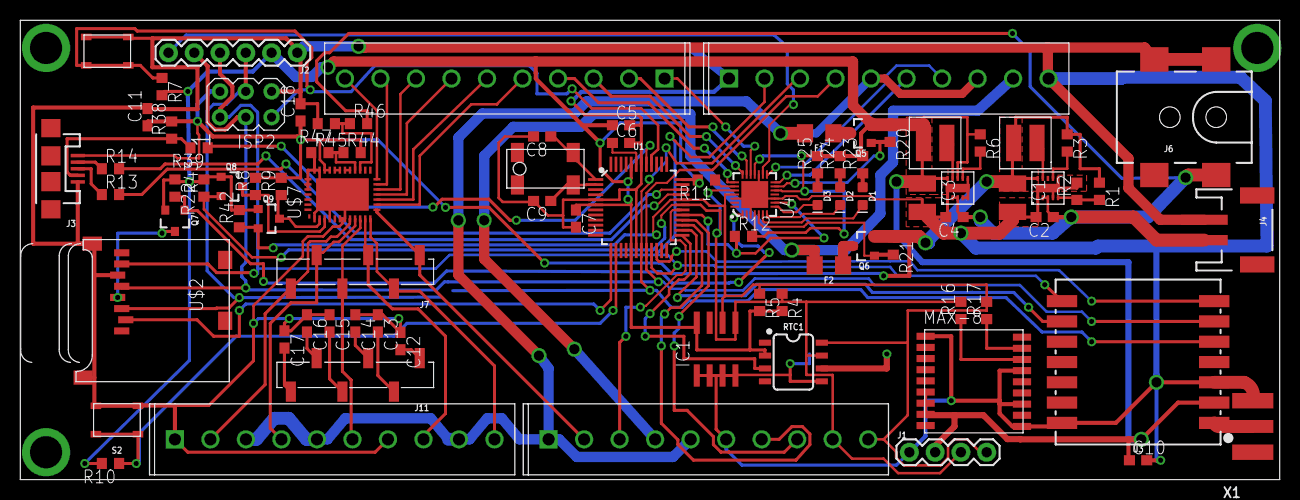
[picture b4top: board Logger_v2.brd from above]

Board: 2 copper layers, 124.1 x 45.3 mm, 87 parts (1 on the bottom side), 83 nets.

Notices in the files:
parts and their libraries:
SparkFun-LED: Licensing: Creative Commons ShareAlike 4.0 International - https://creativecommons.org/licenses/by-sa/4.0
SparkFun-Connectors: Licensing: CC v3.0 Share-Alike You are welcome to use this library for commercial purposes.
rc-master-smd: Copyright (C) 2007, Bob Starr
